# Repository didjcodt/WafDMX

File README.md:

# WafDMX
Ultra-simple DMX controller for LED strips

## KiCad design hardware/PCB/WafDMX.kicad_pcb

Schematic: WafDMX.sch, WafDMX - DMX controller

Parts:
C1, C7, C9, C18: 1 uF; C_0603_1608Metric
C2: 470pF; C_0603_1608Metric
C3, C4, C5, C6, C12, C14, C15, C16, C17: 0.1 uF; C_0603_1608Metric
C8: 10 uF; C_1206_3216Metric
C10: 0.1uF; C_0603_1608Metric
C11: 0.01 uF; C_0603_1608Metric
C13: 22 uF; C_1206_3216Metric
J1: Wuerth_7499010121A; RJ45_Wuerth_7499010121A_Horizontal
J2: Screw_Terminal_01x02; TerminalBlock_WAGO_2604-1102_2x05_P5.00mm_30Degree
J3: USB_B_Micro; USB_Micro-B_Molex-105017-0001
J4: Conn_01x04_Female; PinHeader_1x04_P2.54mm_Vertical
J5: XLR3; XLR_Neutrik_NC3FAAH_Horizontal
J6: XLR3; XLR_Neutrik_NC3MAAH_Horizontal
JP1: SolderJumper_2_Open; SolderJumper-2_P1.3mm_Open_Pad1.0x1.5mm
L1: 2.0A/0.050DCR; L_0603_1608Metric
P1, P2, P3, P4: POW_OUT
Q1: MMDT2222A; SOT-363_SC-70-6
R1, R5: 0R; R_0603_1608Metric
R2: 330R; R_0603_1608Metric
R3, R4, R6, R9, R11, R12: 10K; R_0603_1608Metric
R7: 12K1 1%; R_0603_1608Metric
R8, R10: 33R; R_0603_1608Metric
TP1, TP2, TP3, TP4, TP5, TP6, TP7, TP8, TP9, TP10, TP11: TestPoint; TestPoint_THTPad_1.0x1.0mm_Drill0.5mm
U1: AMS1117-3.3; SOT-223-3_TabPin2
U2: LAN8720A; QFN-24-1EP_4x4mm_P0.5mm_EP2.6x2.6mm
U3: CH340C; SOP-16_4.4x10.4mm_P1.27mm
U4: ESP32-WROOM-32D; ESP32-WROOM-32
U5: MAX3485; SOIC-8_3.9x4.9mm_P1.27mm
X1: ASV-50MHz; Oscillator_SMD_Abracon_ASV-4Pin_7.0x5.1mm

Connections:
+3V3: C3.1, C6.1, C8.1, C9.1, C12.1, C13.1, C14.1, C15.1, C17.1, C18.1, J1.10, J1.12, L1.1, R3.2, R4.2, R5.1, R9.1, U1.2, U2.9, U3.16 (VCC), U4.2, U5.8, X1.4; also elsewhere on the board
/5V_SPI_CLK: J4.2; also elsewhere on the board
/5V_SPI_MOSI: J4.3; also elsewhere on the board
/DMX_DE: U4.19, U5.3
/DMX_MAX_IN: U4.18, U5.4
/DMX_MAX_OUT: U4.17, U5.1
/DMX_RE: U4.20, U5.2
/DTR: Q1.1, R12.2, U3.13 (DTR)
/EMAC_RXD0: U2.8, U4.10
/EMAC_RXD1: U2.7, U4.11
/EMAC_RX_DV: U2.11, U4.12
/EMAC_TXD0: U2.17, U4.31
/EMAC_TXD1: U2.18, U4.36
/EMAC_TX_EN: U2.16, U4.33
/EN: C16.1, Q1.4, R9.2, U4.3
/ESP32_RX: U3.2 (TXD), U4.34
/ESP32_TX: U3.3 (RXD), U4.35
/IO0: Q1.6, R10.2, U4.25
/PHY_CLK: R8.2, R10.1, X1.3
/PHY_CLK_EN: R6.1, U4.27, X1.1
/PHY_LED_LNK_ACT: R1.1, U2.3
/PHY_LED_SPEED: R2.1, U2.2
/PHY_POWER: U2.15, U4.28
/PHY_RX_N: J1.6, U2.22
/PHY_RX_P: J1.4, U2.23
/PHY_TX_N: J1.3, U2.20
/PHY_TX_P: J1.1, U2.21
/RTS: Q1.3, R11.2, U3.14 (RTS)
/SMI_MDC: U2.13, U4.37
/SMI_MDIO: R3.1, U2.12, U4.30
/SPI_CLK: U4.13; also elsewhere on the board
/SPI_MOSI: U4.16; also elsewhere on the board
/SPI_OE: U4.21; also elsewhere on the board
/USB_DN: J3.2, U3.5 (UD_N)
/USB_DP: J3.3, U3.6 (UD_P)
GND: C1.1, C2.2, C3.2, C4.2, C5.2, C6.2, C7.2, C8.2, C9.2, C10.2, C11.2, C12.2, C13.2, C14.2, C15.2, C16.2, C17.2, C18.2, J1.8, J2.1, J3.5, J3.6, J4.4, J5.1, J6.1, R6.2, R7.1, U1.1, U2.25, U3.1 (GND), U4.1, U4.15, U4.38, U5.5, X1.2; also elsewhere on the board
unnamed: C1.2, C2.1, U2.6
unnamed: C4.1, C5.1, L1.2, U2.1, U2.19
unnamed: C10.1, J1.2, J1.5, R5.2
unnamed: C11.1, P3.~, U3.4 (V3)
unnamed: J1.9, R1.2
unnamed: J1.11, R2.2
unnamed: J4.1, JP1.2
unnamed: J5.2, J6.2, U5.7
unnamed: J5.3, J6.3, U5.6
unnamed: Q1.2, R11.1
unnamed: Q1.5, R12.1
unnamed: R4.1, U2.10
unnamed: R7.2, U2.24
unnamed: R8.1, U2.5
unnamed: TP1.1, U4.24
unnamed: TP2.1, U4.26
unnamed: TP3.1, U4.29
unnamed: TP4.1, U4.14
unnamed: TP5.1, U4.23
unnamed: TP7.1, U4.22
unnamed: TP8.1, U4.8
unnamed: TP9.1, U4.9
unnamed: TP10.1, U4.6
unnamed: TP11.1, U4.7
VCC: C7.1, J2.2, JP1.1, U1.3; also elsewhere on the board

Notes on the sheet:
USE HSPI
All resistors MUST be close to LAN8720A
MODE[2:0] = 111 -> Auto negociation PHYAD0 = 1 -> PHY1

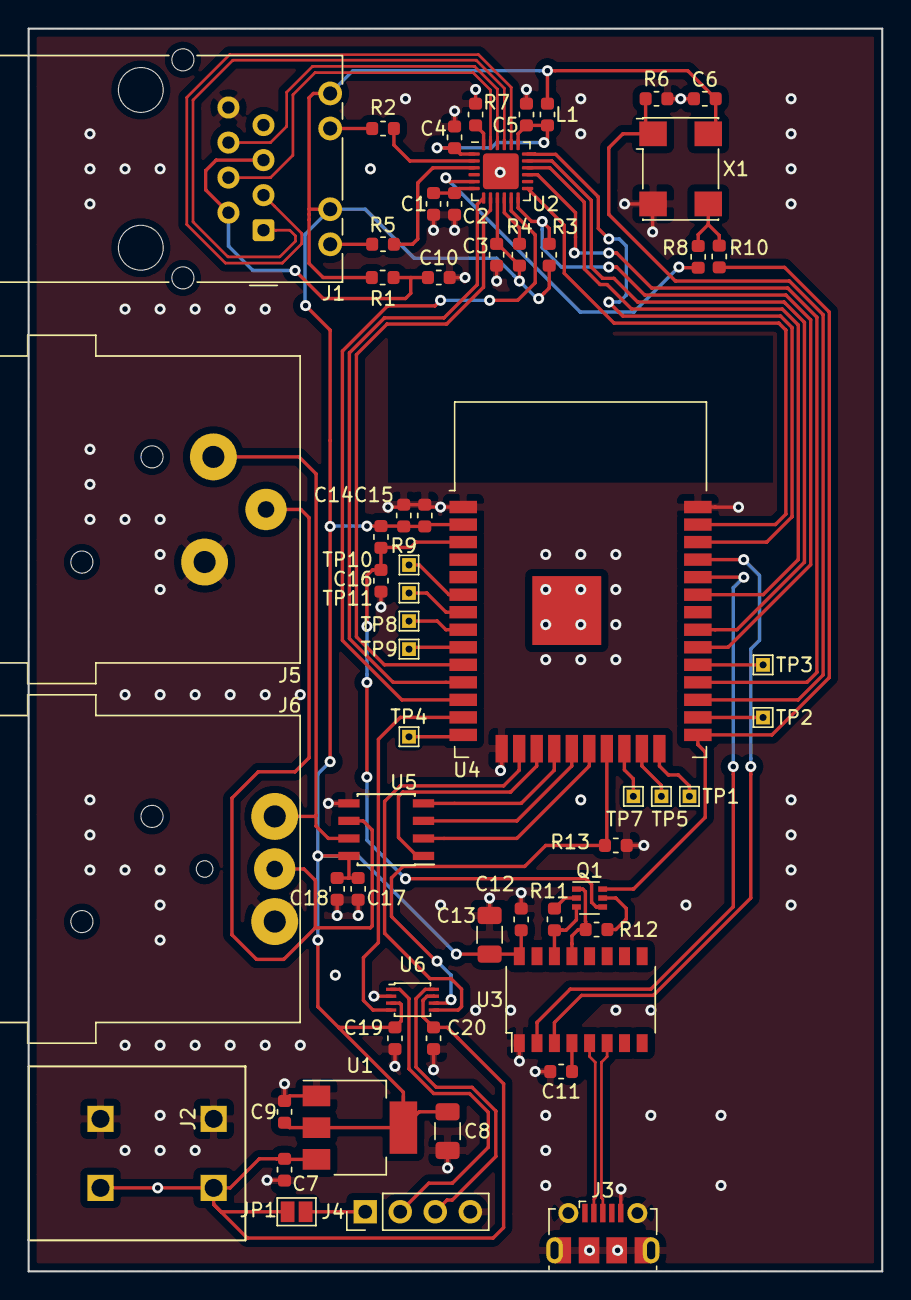
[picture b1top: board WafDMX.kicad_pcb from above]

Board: 2 copper layers, 61.8 x 90.0 mm, 59 parts (0 on the bottom side), 61 nets.

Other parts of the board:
C19, C20: 0.1 uF; C_0603_1608Metric
R13: R_Small; R_0603_1608Metric
U6: TXB0102DCU; VSSOP-8_2.4x2.1mm_P0.5mm

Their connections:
+3V3: C19.1, U6.3; also elsewhere on the board
/5V_SPI_CLK: U6.1; also elsewhere on the board
/5V_SPI_MOSI: U6.8; also elsewhere on the board
/SPI_CLK: U6.4; also elsewhere on the board
/SPI_MOSI: U6.5; also elsewhere on the board
/SPI_OE: R13.1, U6.6; also elsewhere on the board
GND: C19.2, C20.2, R13.2, U6.2; also elsewhere on the board
VCC: C20.1, U6.7; also elsewhere on the board

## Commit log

2019-06-03 Add ESP32, LDO, MAX3485 and LAN8720A
2019-06-04 Add LAN8720A and trace
2019-06-04 Use A3 paper size, add CH340C
2019-06-05 Add Makefile
2019-06-05 Place components
2019-06-06 Change Testpoints to TH, start placing
2019-06-06 First routing of PCB
2019-06-08 Add XLR Connector
2019-06-09 Add routing
2019-06-09 Add 3d shapes
2019-06-09 Add 3V3-5V level shifter
2019-06-09 Add 3dshape for rj45
2019-06-11 Add farnell references
2019-06-25 Add base project using APA102/MQTT bridge
2019-06-30 Add Art-Net DMX opcode support
2019-06-30 Add clang-format
2019-06-30 Add other Art-Net opcodes in defines
2019-07-02 Add Ethernet support
2019-07-02 Add pre-setup sdkconfig
2019-07-02 Add ugly hacks to make everything work with either net stack
2019-07-08 Temp
2019-07-23 Add new artnet opcodes
2019-07-23 Fix CH340C D-/D+ inversion
2019-07-23 Uniformise component values
2019-07-23 Mode SPI_OE on GPIO13
2019-08-26 Add FPGA and LCD screen, bump to v2
